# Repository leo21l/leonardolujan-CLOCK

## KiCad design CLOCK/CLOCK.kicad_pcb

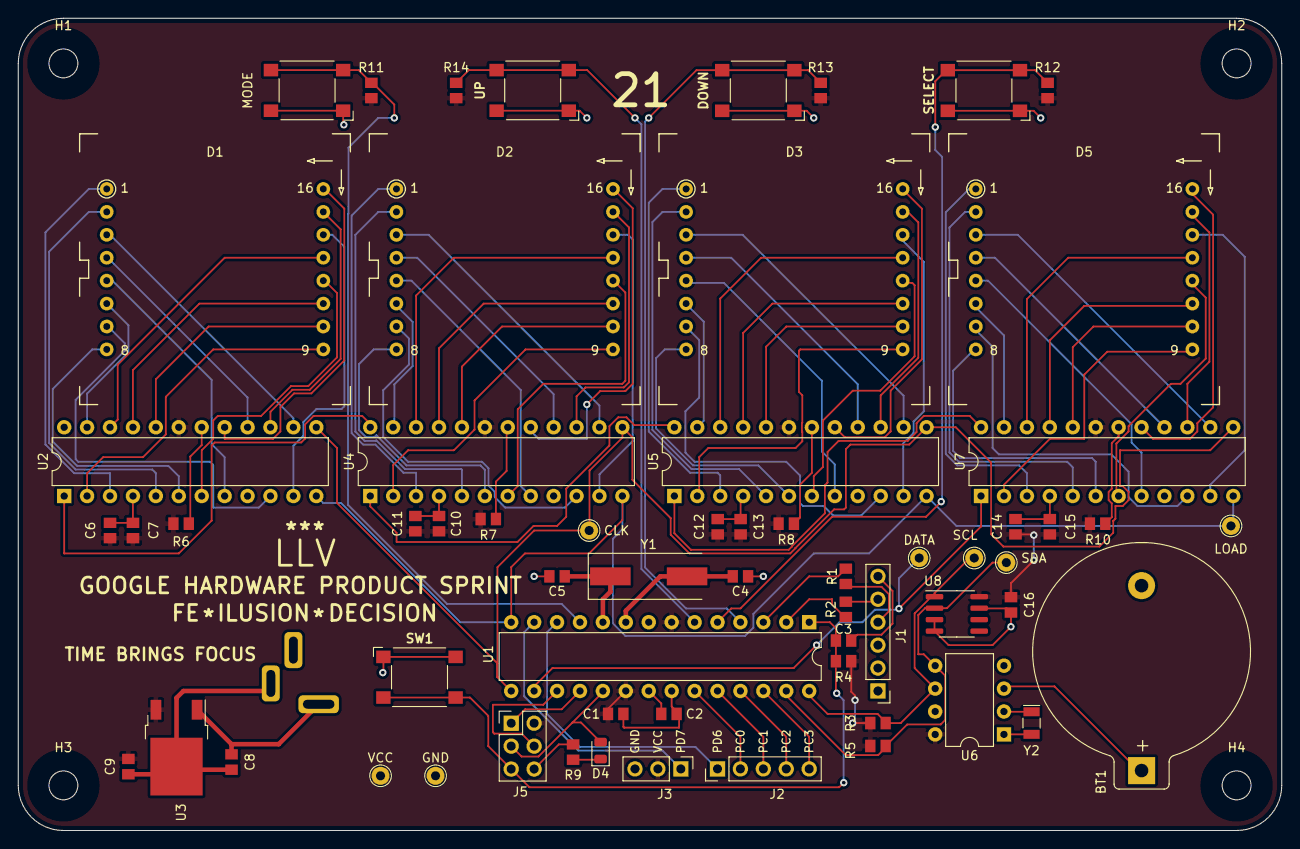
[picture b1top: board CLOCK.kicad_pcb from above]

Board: 2 copper layers, 140.0 x 90.0 mm, 67 parts (1 on the bottom side), 105 nets.

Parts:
BT1: Battery_Cell; BatteryHolder_Keystone_106_1x20mm
C1, C2, C3, C6, C9, C10, C12, C14, C16: C_0805_0.1uf; C_0805_2012Metric
C4, C5: C_0805_22pf; C_0805_2012Metric
C7, C11, C13, C15: C_0805_10uf; C_0805_2012Metric
C8: C_0805_1uf; C_0805_2012Metric
CLK: TestPoint; TestPoint_THTPad_D2.0mm_Drill1.0mm
D1, D2, D3, D5: KWM-30881CVB
D4: LED_0805; LED_0805_2012Metric
DATA: TestPoint; TestPoint_THTPad_D2.0mm_Drill1.0mm
DOWN: Omron_B3F_SPST; SW_SPST_Omron_B3FS-100xP
GND: TestPoint; TestPoint_THTPad_D2.0mm_Drill1.0mm
H1, H2, H3, H4: MountingHole; MountingHole_3.2mm_M3
J1: Conn_01x06; PinHeader_1x06_P2.54mm_Vertical
J2: Conn_01x05; PinHeader_1x05_P2.54mm_Vertical
J3: Conn_01x03; PinHeader_1x03_P2.54mm_Vertical
J4: Power_inlet_vertical; Wurth-694106402002
J5: Conn_02x03_Odd_Even; PinHeader_2x03_P2.54mm_Vertical
LOAD: TestPoint; TestPoint_THTPad_D2.0mm_Drill1.0mm
MODE: Omron_B3F_SPST; SW_SPST_Omron_B3FS-100xP
R1, R2: R_0805_47; R_0805_2012Metric
R3, R5: R_0805_4.7K; R_0805_2012Metric
R4, R6, R7, R8, R10, R11, R12, R13, R14: R_0805_10K; R_0805_2012Metric
R9: R_0805_2.2K; R_0805_2012Metric
SCL: TestPoint; TestPoint_THTPad_D2.0mm_Drill1.0mm
SDA: TestPoint; TestPoint_THTPad_D2.0mm_Drill1.0mm
SELECT: Omron_B3F_SPST; SW_SPST_Omron_B3FS-100xP
SW1: Omron_B3F_SPST; SW_SPST_Omron_B3FS-100xP
U1: ATmega328-PU; DIP-28_W7.62mm
U2, U4, U5, U7: MAX7219; DIP-24_W7.62mm
U3: L7805; TO-252-2
U6: DS1307_DIP-8; DIP-8_W7.62mm
U8: ADT7410; SOIC-8_3.9x4.9mm_P1.27mm
UP: Omron_B3F_SPST; SW_SPST_Omron_B3FS-100xP
VCC: TestPoint; TestPoint_THTPad_D2.0mm_Drill1.0mm
Y1: Crystal_16MHz; Crystal_SMD_HC49-SD
Y2: Crystal_32768Hz; Crystal_SMD_2Pin_3.2x1.5mm

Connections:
1DIG_0: D1.9 (R1), U2.2 (DIG_0)
1DIG_1: D1.14 (R2), U2.11 (DIG_1)
1DIG_2: D1.8 (R3), U2.6 (DIG_2)
1DIG_3: D1.12 (R4), U2.7 (DIG_3)
1DIG_4: D1.1 (R5), U2.3 (DIG_4)
1DIG_5: D1.7 (R6), U2.10 (DIG_5)
1DIG_6: D1.2 (R7), U2.5 (DIG_6)
1DIG_7: D1.5 (R8), U2.8 (DIG_7)
1SEG_A: D1.3 (C2), U2.14 (SEG_A)
1SEG_B: D1.4 (C3), U2.16 (SEG_B)
1SEG_C: D1.10 (C4), U2.20 (SEG_C)
1SEG_D: D1.6 (C5), U2.23 (SEG_D)
1SEG_DP: D1.13 (C1), U2.22 (SEG_DP)
1SEG_E: D1.11 (C6), U2.21 (SEG_E)
1SEG_F: D1.15 (C7), U2.15 (SEG_F)
1SEG_G: D1.16 (C8), U2.17 (SEG_G)
2DIG_0: D2.9 (R1), U4.2 (DIG_0)
2DIG_1: D2.14 (R2), U4.11 (DIG_1)
2DIG_2: D2.8 (R3), U4.6 (DIG_2)
2DIG_3: D2.12 (R4), U4.7 (DIG_3)
2DIG_4: D2.1 (R5), U4.3 (DIG_4)
2DIG_5: D2.7 (R6), U4.10 (DIG_5)
2DIG_6: D2.2 (R7), U4.5 (DIG_6)
2DIG_7: D2.5 (R8), U4.8 (DIG_7)
2SEG_A: D2.3 (C2), U4.14 (SEG_A)
2SEG_B: D2.4 (C3), U4.16 (SEG_B)
2SEG_C: D2.10 (C4), U4.20 (SEG_C)
2SEG_D: D2.6 (C5), U4.23 (SEG_D)
2SEG_DP: D2.13 (C1), U4.22 (SEG_DP)
2SEG_E: D2.11 (C6), U4.21 (SEG_E)
2SEG_F: D2.15 (C7), U4.15 (SEG_F)
2SEG_G: D2.16 (C8), U4.17 (SEG_G)
3DIG_0: D3.9 (R1), U5.2 (DIG_0)
3DIG_1: D3.14 (R2), U5.11 (DIG_1)
3DIG_2: D3.8 (R3), U5.6 (DIG_2)
3DIG_3: D3.12 (R4), U5.7 (DIG_3)
3DIG_4: D3.1 (R5), U5.3 (DIG_4)
3DIG_5: D3.7 (R6), U5.10 (DIG_5)
3DIG_6: D3.2 (R7), U5.5 (DIG_6)
3DIG_7: D3.5 (R8), U5.8 (DIG_7)
3SEG_A: D3.3 (C2), U5.14 (SEG_A)
3SEG_B: D3.4 (C3), U5.16 (SEG_B)
3SEG_C: D3.10 (C4), U5.20 (SEG_C)
3SEG_D: D3.6 (C5), U5.23 (SEG_D)
3SEG_DP: D3.13 (C1), U5.22 (SEG_DP)
3SEG_E: D3.11 (C6), U5.21 (SEG_E)
3SEG_F: D3.15 (C7), U5.15 (SEG_F)
3SEG_G: D3.16 (C8), U5.17 (SEG_G)
4DIG_0: D5.9 (R1), U7.2 (DIG_0)
4DIG_1: D5.14 (R2), U7.11 (DIG_1)
4DIG_2: D5.8 (R3), U7.6 (DIG_2)
4DIG_3: D5.12 (R4), U7.7 (DIG_3)
4DIG_4: D5.1 (R5), U7.3 (DIG_4)
4DIG_5: D5.7 (R6), U7.10 (DIG_5)
4DIG_6: D5.2 (R7), U7.5 (DIG_6)
4DIG_7: D5.5 (R8), U7.8 (DIG_7)
4SEG_A: D5.3 (C2), U7.14 (SEG_A)
4SEG_B: D5.4 (C3), U7.16 (SEG_B)
4SEG_C: D5.10 (C4), U7.20 (SEG_C)
4SEG_D: D5.6 (C5), U7.23 (SEG_D)
4SEG_DP: D5.13 (C1), U7.22 (SEG_DP)
4SEG_E: D5.11 (C6), U7.21 (SEG_E)
4SEG_F: D5.15 (C7), U7.15 (SEG_F)
4SEG_G: D5.16 (C8), U7.17 (SEG_G)
BTN_DWN: DOWN.3 (B), DOWN.4 (B), R13.2, U1.4 (INT0/PD2)
BTN_MODE: MODE.3 (B), MODE.4 (B), R11.2, U1.11 (OC0B/PD5)
BTN_SEL: R12.2, SELECT.3 (B), SELECT.4 (B), U1.5 (INT1/PD3)
BTN_UP: R14.2, U1.6 (PD4), UP.3 (B), UP.4 (B)
CLK: CLK.1, U1.15 (OC1A/PB1), U2.13 (CLK), U4.13 (CLK), U5.13 (CLK), U7.13 (CLK)
DDATA: DATA.1, U1.16 (OC1B/PB2), U7.1 (DIN)
DLOAD: LOAD.1, U1.14 (PB0), U2.12 (LOAD), U4.12 (LOAD), U5.12 (LOAD), U7.12 (LOAD)
GND: BT1.2 (-), C1.2, C2.2, C4.1, C5.2, C6.2, C7.1, C8.2, C9.2, C10.2, C11.1, C12.2, C13.1, C14.2, C15.1, C16.2, DOWN.1 (A), DOWN.2 (A), GND.1, J1.1, J1.2, J3.3, J4.2 (OUT), J5.6, MODE.1 (A), MODE.2 (A), R9.2, SELECT.1 (A), SELECT.2 (A), SW1.1 (A), SW1.2 (A), U1.8 (GND), U1.22 (GND), U2.4 (GND), U2.9 (GND), U3.2 (GND), U4.4 (GND), U4.9 (GND), U5.4 (GND), U5.9 (GND), U6.4 (GND), U7.4 (GND), U7.9 (GND), U8.3 (A0), U8.4 (A1), U8.7 (GND), UP.1 (A), UP.2 (A)
LED_SCK: D4.2 (A), J5.3, U1.19 (SCK/PB5)
MISO: J5.1, U1.18 (MISO/PB4)
MOSI: J5.4, U1.17 (MOSI/PB3)
unnamed: BT1.1 (+), U6.3 (VBAT)
unnamed: C2.1, U1.21 (AREF)
unnamed: C3.2, J1.6
unnamed: C4.2, U1.9 (XTAL1/PB6), Y1.2
unnamed: C5.1, U1.10 (XTAL2/PB7), Y1.1
unnamed: C8.1, J4.1 (POLE), U3.1 (IN)
unnamed: D4.1 (K), R9.1
unnamed: J1.4, R1.2
unnamed: J1.5, R2.2
unnamed: R6.2, U2.18 (ISET)
unnamed: R7.1, U4.18 (ISET)
unnamed: R8.1, U5.18 (ISET)
unnamed: R10.1, U7.18 (ISET)
unnamed: U2.1 (DIN), U4.24 (DOUT)
unnamed: U4.1 (DIN), U5.24 (DOUT)
unnamed: U5.1 (DIN), U7.24 (DOUT)
unnamed: U6.1 (X1), Y2.2
unnamed: U6.2 (X2), Y2.1
PC0: J2.2, U1.23 (ADC0/PC0)
PC1: J2.3, U1.24 (ADC1/PC1)
PC2: J2.4, U1.25 (ADC2/PC2)
PC3: J2.5, U1.26 (ADC3/PC3)
PD6: J2.1, U1.12 (OC0A/PD6)
PD7: J3.1, U1.13 (PD7)
RESET: C3.1, J5.5, R4.1, SW1.3 (B), SW1.4 (B), U1.1 (~RESET/PC6)
RXD: R2.1, U1.2 (RXD/PD0)
SCL: R3.2, SCL.1, U1.28 (SCL/PC5), U6.6 (SCL), U8.1 (SCL)
SDA: R5.2, SDA.1, U1.27 (SDA/PC4), U6.5 (SDA), U8.2 (SDA)
TXD: R1.1, U1.3 (TXD/PD1)
VCC: C1.1, C6.1, C7.2, C9.1, C10.1, C11.2, C12.1, C13.2, C14.1, C15.2, C16.1, J3.2, J5.2, R3.1, R4.2, R5.1, R6.1, R7.2, R8.2, R10.2, R11.1, R12.1, R13.1, R14.1, U1.7 (VCC), U1.20 (AVCC), U2.19 (V+), U3.3 (OUT), U4.19 (V+), U5.19 (V+), U6.8 (VCC), U7.19 (V+), U8.8 (VDD), VCC.1

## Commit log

2022-06-13 Firmware
    WEEK 1 deliverable
2022-06-20 WEEK2
    WEEK2
2022-06-29 WEEK 3
2022-07-12 WEEK4/5
    PROGRSSING
2022-07-13 FINAL DESIGN
    TIME TO ROUTE :)
2022-07-18 WEEK6
    UPLOADING PCB
2022-07-18 1
    1
2022-07-22 GERBER OUT
    LLV-BOARD
2022-07-22 COMMIT
    :)
2022-07-24 GERBER OUT
    FINAL COMMIT
2022-07-24 GERB
    GERB
2022-07-24 GERBER OUT
    :)
2022-07-24 GERBER OUT
    :+1:
2022-08-04 commit
    commit
2022-08-12 Temp mode
2023-01-05 Created using Colaboratory
